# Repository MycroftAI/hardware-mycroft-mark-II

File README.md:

# Mycroft Mark II Hardware

*⛵️ Note that this repository is a work-in-progress. It will be updated and improved on over time.*

This repository contains all of the designs and technical details of the Mycroft Mark II Prototypes.

Each sub-directory represents a prototype device. Currently this consists of:
- [Mark II RPi OTS](./mark-II-rpi-ots) - the first Mark II prototype released in February 2020 made from off-the-shelf components. [Deprecated]
- [Mark II RPi DevKit](./mark-II-Rpi-devkit) - the second iteration of the Mark II prototype. This includes a custom daughterboard (SJ201) that integrates the components from the OTS prototype into a single PCB.

## Our open hardware principles
* **Copy our designs** – build your own Mycroft Mark 2 - Raspberry Pi Edition or its individual parts
* **Modify our designs** – remixing is encouraged
* **Sell products based on our designs** – commercial use is permitted
* **Always keep the open license** – contribute your output back to the community
* **Credit the original author(s)** – like they do in science

## Feedback or ideas

We are always keen to hear from the community about ways to improve these designs. Whether you're a hacker, maker, engineer, or something else - join us in the:
- [Community Forums](https://community.mycroft.ai)
- [Community Chat](https://chat.mycroft.ai)
- or email us at [dev@mycroft.ai](mailto:dev@mycroft.ai)

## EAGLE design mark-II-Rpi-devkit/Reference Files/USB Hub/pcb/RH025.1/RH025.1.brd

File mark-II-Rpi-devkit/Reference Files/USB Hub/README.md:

### Description

USB hub for the Raspberry Pi Zero

### Features

- 4 x USB 2.0 ports
- Micro USB upstream connector
- FE1.1s USB hub chip
- Solder pins for direct connection to the Raspberry Pi Zero
- Power jack connector for external 5v power source
- Optional jumpers to take power from upstream connector
- LED status indicators for each downstream port

### Modes of use

#### 1. Direct solder

You can solder 4 wires directly between the Zero and the hub using 4 pads exposed on both the hub and the Zero. This will connect the 5V, GND, USB D+ and USB D-.

You can then either power the board either using the USB power connector on the Zero, or using the power jack on the hub.

This is the neatest option, although does involve soldering.

#### 2. USB connection

Using a USB OTG cable, or a micro USB to micro USB you can connect the data USB port on the Zero to the upstream USB connector on the side of the hub. Adding the 2 power jumpers allows the hub to use power supplied to the Zero though the power USB connector.

Alternatively, remove the power jumpers and power the hub through the external power jack.

Although a USB cable is needed to connect the two in this mode, no soldering is required.

#### 3. Standalone hub

This board can be used as a regular USB hub, either using power from the upstream USB connector, or through the power jack and external power supply.

### Licence

This work is licensed under the Creative Commons Attribution-ShareAlike 4.0 International License. 
To view a copy of this license, visit http://creativecommons.org/licenses/by-sa/4.0/

Designed by <a xmlns:cc="http://creativecommons.org/ns#" href="http://www.richardhawthorn.com" property="cc:attributionName" rel="cc:attributionURL" target="_blank">Richard Hawthorn</a><br />

Based on design by @MakerBro, https://acrobotic.com

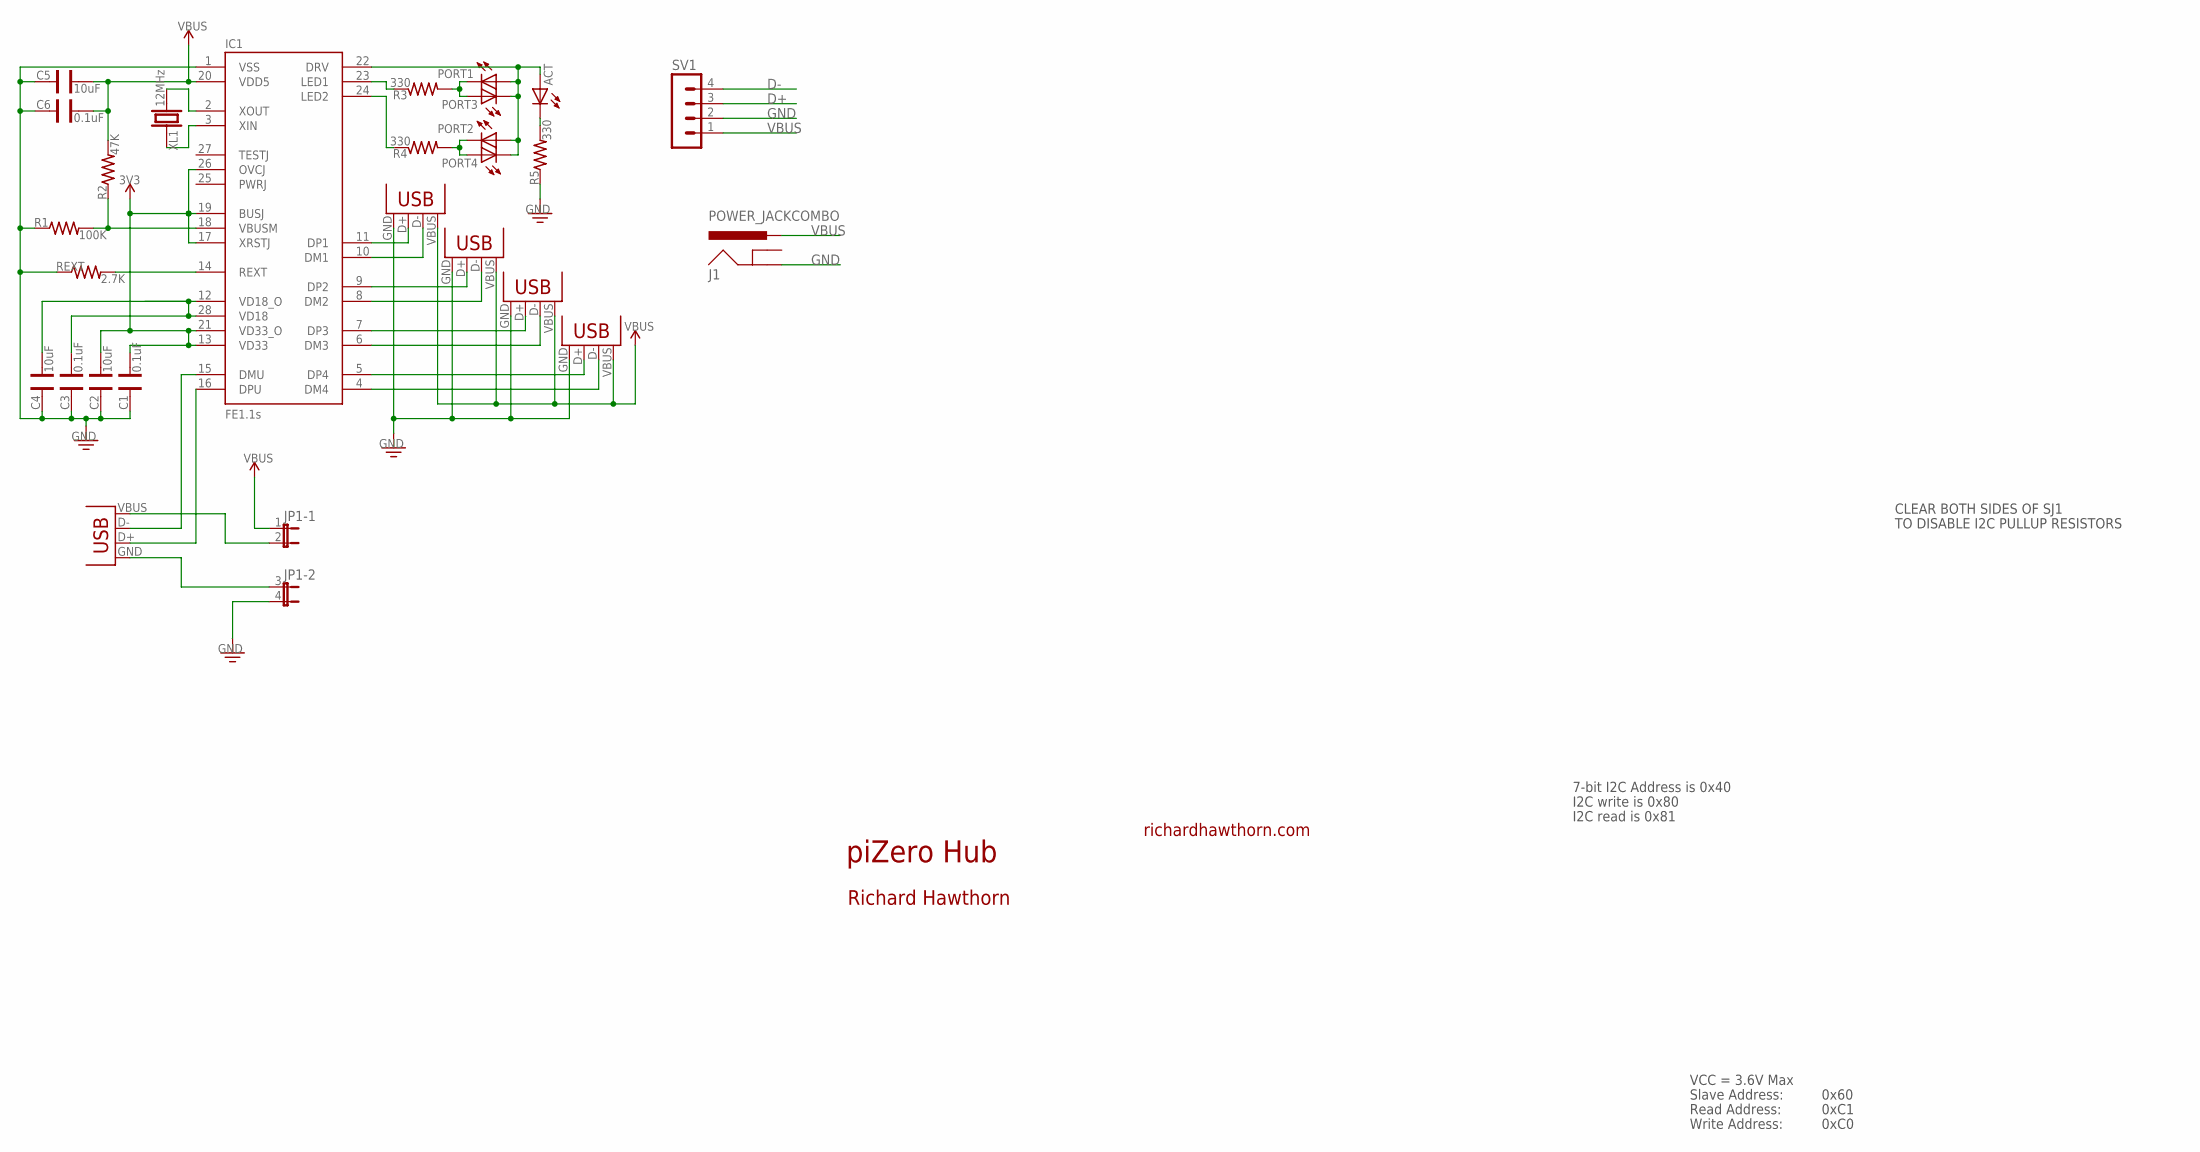
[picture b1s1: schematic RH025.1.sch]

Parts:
ACT: LED0603; LED-0603
C1, C3, C6: 0.1uF; CAP-0603
C2, C4, C5: 10uF; CAP-0603
IC1: FE1.1S; FE1.1S_SSOP-28
J1: POWER_JACKCOMBO; POWER_JACK_COMBO
JP1: JP2QE; JP2Q
PORT1, PORT2, PORT3, PORT4: LED0603; LED-0603
R1: 100K; RES-0603
R2: 47K; RES-0603
R3, R4, R5: 330; RES-0603
REXT: 2.7K; RES-0603
SV1: MA04-1
USB1: USBMICROB-PTH; USB-MICROB-TH
USB2, USB3, USB4, USB5: USBA-PTH; USB-A-F-PTH
XL1: 12MHz; HC49UP

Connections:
3V3: C1.1, C2.1, IC1.13 (VD33), IC1.17 (XRSTJ), IC1.19 (BUSJ), IC1.21 (VD33_O), IC1.26 (OVCJ)
D+: IC1.16 (DPU), SV1.3, USB1.D+
D-: IC1.15 (DMU), SV1.4, USB1.D-
GND: C1.2, C2.2, C3.2, C4.2, C5.2, C6.2, IC1.1 (VSS), J1.GND@1 (GND), JP1.4 (2), R1.1, R5.1, REXT.1, SV1.2, USB2.GND, USB3.GND, USB4.GND, USB5.GND
unnamed: IC1.14 (REXT), REXT.2
unnamed: JP1.2, USB1.VBUS
unnamed: JP1.3 (1), USB1.GND
unnamed: PORT2.C, PORT4.A, R4.2
unnamed: IC1.2 (XOUT), XL1.2
unnamed: C3.1, C4.1, IC1.12 (VD18_O), IC1.28 (VD18)
unnamed: IC1.3 (XIN), XL1.1
unnamed: IC1.11 (DP1), USB5.D+
unnamed: IC1.10 (DM1), USB5.D-
unnamed: IC1.18 (VBUSM), R1.2, R2.1
unnamed: IC1.9 (DP2), USB4.D+
unnamed: IC1.8 (DM2), USB4.D-
unnamed: IC1.7 (DP3), USB3.D+
unnamed: IC1.6 (DM3), USB3.D-
unnamed: IC1.5 (DP4), USB2.D+
unnamed: IC1.4 (DM4), USB2.D-
unnamed: PORT1.C, PORT3.A, R3.2
unnamed: ACT.C, R5.2
unnamed: IC1.23 (LED1), R3.1
unnamed: IC1.24 (LED2), R4.1
unnamed: ACT.A, IC1.22 (DRV), PORT1.A, PORT2.A, PORT3.C, PORT4.C
VBUS: C5.1, C6.1, IC1.20 (VDD5), J1.POWER (PWR), JP1.1, R2.2, SV1.1, USB2.VBUS, USB3.VBUS, USB4.VBUS, USB5.VBUS

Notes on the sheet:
piZero Hub
richardhawthorn.com
Richard Hawthorn
CLEAR BOTH SIDES OF SJ1
TO DISABLE I2C PULLUP RESISTORS
7-bit I2C Address is 0x40
I2C write is 0x80
I2C read is 0x81
VCC = 3.6V Max
Read Address:
Write Address:
Slave Address:
0x60
0xC1
0xC0

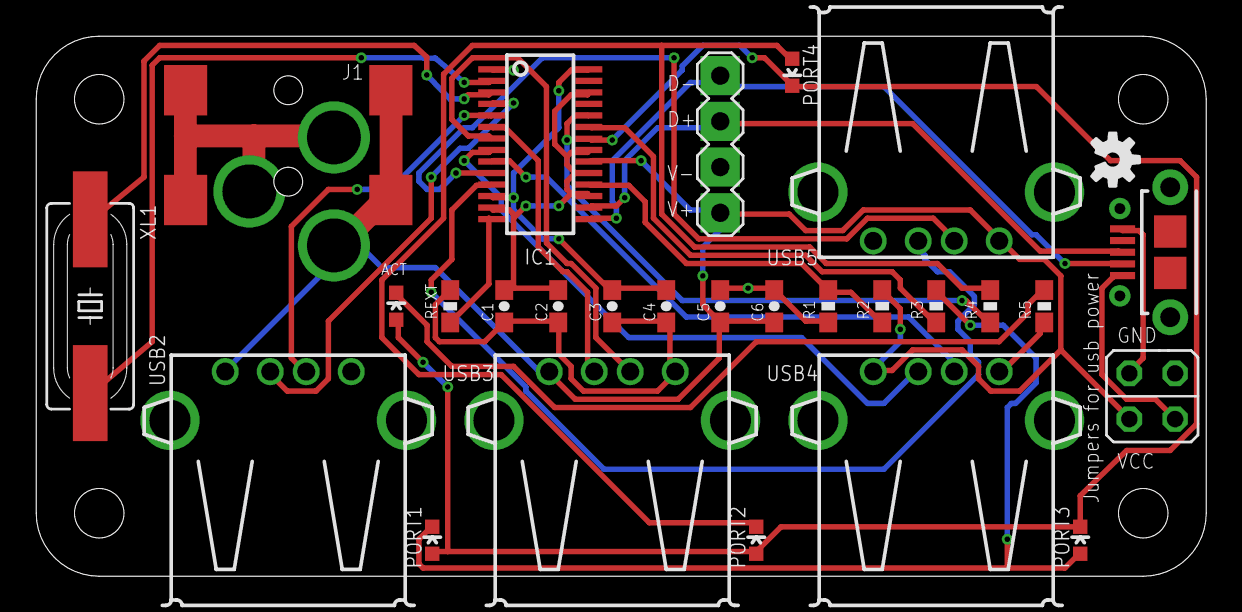
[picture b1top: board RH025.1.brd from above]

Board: 2 copper layers, 65.0 x 30.0 mm, 28 parts (0 on the bottom side), 26 nets.

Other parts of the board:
U$3: OSHW-LOGO-S

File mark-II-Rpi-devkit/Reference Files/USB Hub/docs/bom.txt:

Partlist

Qty Value           Device          Package          Parts                                             
5   LED             LED0603         LED-0603         ACT, PORT1, PORT2, PORT3, PORT4                             
3   0.1uF           CAP0603         CAP-0603         C1, C3, C6                                          
1   100K            RES0603         RES-0603         R1                              
3   10uF            CAP0603         CAP-0603         C2, C4, C5                                          
1   12MHz           CRYSTALHC49UP   HC49UP           XL1                                    
1   2.7K            RES0603         RES-0603         REXT                            
3   330r            RES0603         RES-0603         R3, R4, R5                      
1   47K             RES0603         RES-0603         R2                              
1   FE1.1S          FE1.1S          FE1.1S_SSOP-28   IC1                                                 
1   POWER_JACKCOMBO POWER_JACKCOMBO POWER_JACK_COMBO J1                                  
4   USBA-PTH        USBA-PTH        USB-A-F-PTH      USB2, USB3, USB4, USB5                              
1   USBMICROB-PTH   USBMICROB-PTH   USB-MICROB-TH    USB1

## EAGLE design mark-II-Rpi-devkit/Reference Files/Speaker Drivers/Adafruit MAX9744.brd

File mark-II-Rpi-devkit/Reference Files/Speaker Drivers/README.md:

# PCB files for Adafruit MAX9744 20W stereo audio amplifier board

<a href="http://www.adafruit.com/products/1752"><br/>Click here to purchase one from the Adafruit shop</a>

Pump up the volume with this 20W stereo amplifier! This slim little board has a class D amplifier onboard that can drive 2 channels of 4-8 ohm impedance speakers at 20W each. Power it with 5-12VDC using the onboard DC power jack and plug stereo line level into the 3.5mm stereo headphone jack and jam out with ease. Since it's class D, its completely cool-running, no heat sinks are required and it's extremely efficient - up to 93% efficiency makes it great for portable or battery powered rigs.

We like the MAX9744 amplifier at the heart of this board because its very easy to use, but it also has both analog and digital volume control capability. Use a single 1K½ pot (we include one) to adjust volume analog-style. Or hook it up to your favorite microcontroller and send I2C commands to set 64-steps of volume amplification.

Some great stats about the MAX9744:

- Power from 4.5V-14V DC voltage
- Up to 93% efficient (88-93% typical)
- 20mA quiescent current (or put into shutdown for 1uA quiescent)
- Up to 29.5dB max gain
- Use DC or AC coupled line-level input, up to 3Vpp
- Filterless Spread-Spectrum Modulation Lowers
- Radiated RF Emissions from Speaker Cables
- 20W Stereo Output (4, VDD = 12V, THD+N = 10%)
- Low 0.04% THD+N
- Integrated Click-and-Pop Suppression
- Short-Circuit and Thermal-Overload Protection

We took this lovely chip and wrapped it up into a breakout for you, with polarity-protection, jacks and terminal blocks, i2c level shifting, and a spot to solder in a volume pot.

Each order comes with one MAX9744 breakout board with all surface-mount parts fully assembled and tested. We also include 3 x 2pin and 1 x 3pin terminal blocks, a 470uF power filter capacitor and 1K½ trim pot. To use this board, a little soldering is required to attach the terminal blocks and other components, but its fairly easy and expect it should take less than 15 minutes. [Check out our detailed tutorial for assembly instructions and overall usage](http://learn.adafruit.com/adafruit-20w-stereo-audio-amplifier-class-d-max9744).

Note: The terminal blocks included with your product may be blue or black.

## License

Adafruit invests time and resources providing this open source design, 
please support Adafruit and open-source hardware by purchasing 
products from Adafruit!

Designed by Adafruit Industries.  
Creative Commons Attribution, Share-Alike license, check license.txt for more information
All text above must be included in any redistribution

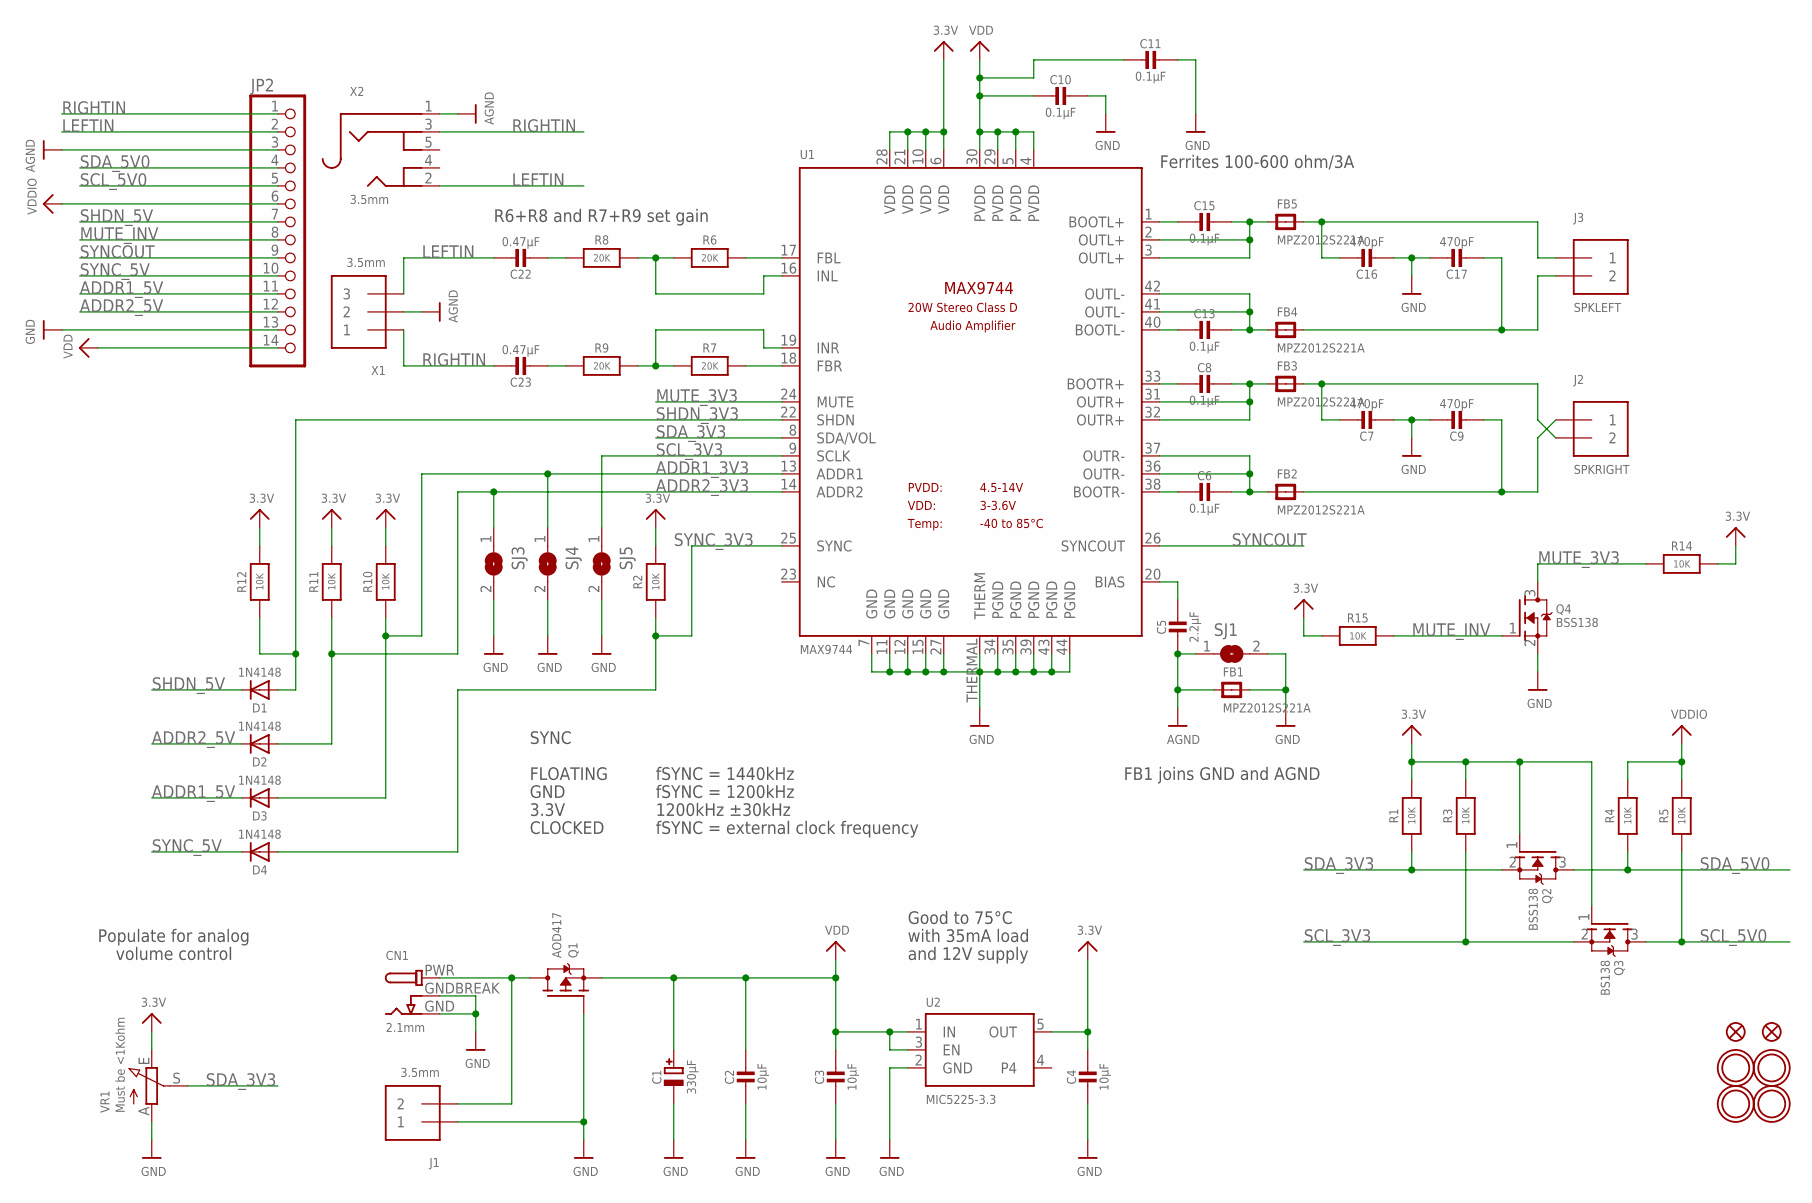
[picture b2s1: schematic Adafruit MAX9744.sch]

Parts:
C1: 330µF; CELEC_3.5MM_8MM
C2, C3, C4: 10µF; 0805-NO
C5: 2.2µF; 0805-NO
C6, C8, C10, C11, C13, C15: 0.1µF; 0805-NO
C7, C9, C16, C17: 470pF; 0805-NO
C22, C23: 0.47µF; 0805-NO
CN1: 2.1mm; DCJACK_2MM_SMT
D1, D2, D3, D4: 1N4148; SOD-323
FB1, FB2, FB3, FB4, FB5: MPZ2012S221A; _0805
FID1, FID2: FIDUCIAL""; FIDUCIAL_1MM
J1: 3.5mm; TERMBLOCK_1X2-3.5MM
J2: SPKRIGHT; TERMBLOCK_1X2-3.5MM
J3: SPKLEFT; TERMBLOCK_1X2-3.5MM
JP2: HEADER-1X14; 1X14_ROUND70
Q1: AOD417; TO252
Q2, Q4: BSS138; SOT23-WIDE
Q3: BS138; SOT23-WIDE
R1, R3, R4, R5, R12: 10K; 0805-NO
R2, R10, R11, R14, R15: 10K; _0805MP
R6, R7, R8, R9: 20K; 0805-NO
SJ1, SJ3, SJ4, SJ5: SOLDERJUMPER; SOLDERJUMPER_ARROW_NOPASTE
U1: MAX9744; TQFN44_7MM
U2: MIC5225-3.3; SOT23-5
U$29, U$38, U$39, U$40: MOUNTINGHOLE2.5_THICK; MOUNTINGHOLE_2.5_PLATED_THICK
VR1: Must be <1Kohm; TRIMPOT_100MILPTH
X1: 3.5mm; TERMBLOCK_1X3-3.5MM
X2: 3.5mm; 4UCONN_19269

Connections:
3.3V: C4.1, Q2.1 (G), Q3.1 (G), R1.2, R2.2, R3.2, R10.2, R11.2, R12.2, R14.2, R15.1, U1.6 (VDD), U1.10 (VDD), U1.21 (VDD), U1.28 (VDD), U2.5 (OUT), VR1.E
ADDR1_3V3: D3.A, R10.1, SJ4.1, U1.13 (ADDR1)
ADDR1_5V: D3.C, JP2.11
ADDR2_3V3: D2.A, R11.1, SJ3.1, U1.14 (ADDR2)
ADDR2_5V: D2.C, JP2.12
AGND: C5.2, FB1.1, JP2.3, SJ1.1, X1.2, X2.1
GND: C1.-, C2.2, C3.2, C4.2, C7.2, C9.1, C10.1, C11.1, C16.2, C17.1, CN1.GND, CN1.GNDBREAK, FB1.2, J1.1, JP2.13, Q1.1 (G), Q4.2 (S), SJ1.2, SJ3.2, SJ4.2, SJ5.2, U1.7 (GND), U1.11 (GND), U1.12 (GND), U1.15 (GND), U1.27 (GND), U1.34 (PGND), U1.35 (PGND), U1.39 (PGND), U1.43 (PGND), U1.44 (PGND), U1.THERMAL (THERM), U2.2 (GND), VR1.A
LEFTIN: C22.1, JP2.2, X1.3, X2.2
MUTE_3V3: Q4.3 (D), R14.1, U1.24 (MUTE)
MUTE_INV: JP2.8, Q4.1 (G), R15.2
unnamed: CN1.PWR, J1.2, Q1.3 (D)
unnamed: C5.1, U1.20 (BIAS)
unnamed: C6.2, U1.38 (BOOTR-)
unnamed: C6.1, FB2.1, U1.36 (OUTR-), U1.37 (OUTR-)
unnamed: C8.2, U1.33 (BOOTR+)
unnamed: C8.1, FB3.1, U1.31 (OUTR+), U1.32 (OUTR+)
unnamed: C7.1, FB3.2, J2.2
unnamed: C9.2, FB2.2, J2.1
unnamed: C13.1, FB4.1, U1.41 (OUTL-), U1.42 (OUTL-)
unnamed: C15.1, FB5.1, U1.2 (OUTL+), U1.3 (OUTL+)
unnamed: C16.1, FB5.2, J3.1
unnamed: C17.2, FB4.2, J3.2
unnamed: C15.2, U1.1 (BOOTL+)
unnamed: C13.2, U1.40 (BOOTL-)
unnamed: R6.2, U1.17 (FBL)
unnamed: R7.2, U1.18 (FBR)
unnamed: R6.1, R8.2, U1.16 (INL)
unnamed: R7.1, R9.2, U1.19 (INR)
unnamed: C22.2, R8.1
unnamed: C23.2, R9.1
RIGHTIN: C23.1, JP2.1, X1.1, X2.3
SCL_3V3: Q3.2 (S), R3.1, SJ5.1, U1.9 (SCLK)
SCL_5V0: JP2.5, Q3.3 (D), R5.1
SDA_3V3: Q2.2 (S), R1.1, U1.8 (SDA/VOL), VR1.S
SDA_5V0: JP2.4, Q2.3 (D), R4.1
SHDN_3V3: D1.A, R12.1, U1.22 (SHDN)
SHDN_5V: D1.C, JP2.7
SYNCOUT: JP2.9, U1.26 (SYNCOUT)
SYNC_3V3: D4.A, R2.1, U1.25 (SYNC)
SYNC_5V: D4.C, JP2.10
VDD: C1.+, C2.1, C3.1, C10.2, C11.2, JP2.14, Q1.2 (S), U1.4 (PVDD), U1.5 (PVDD), U1.29 (PVDD), U1.30 (PVDD), U2.1 (IN), U2.3 (EN)
VDDIO: JP2.6, R4.2, R5.2

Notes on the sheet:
Good to 75°C
with 35mA load
and 12V supply
FB1 joins GND and AGND
SYNC
FLOATING
GND
3.3V
CLOCKED
fSYNC = 1200kHz
fSYNC = 1440kHz
1200kHz ±30kHz
fSYNC = external clock frequency
R6+R8 and R7+R9 set gain
Ferrites 100-600 ohm/3A
Populate for analog
volume control

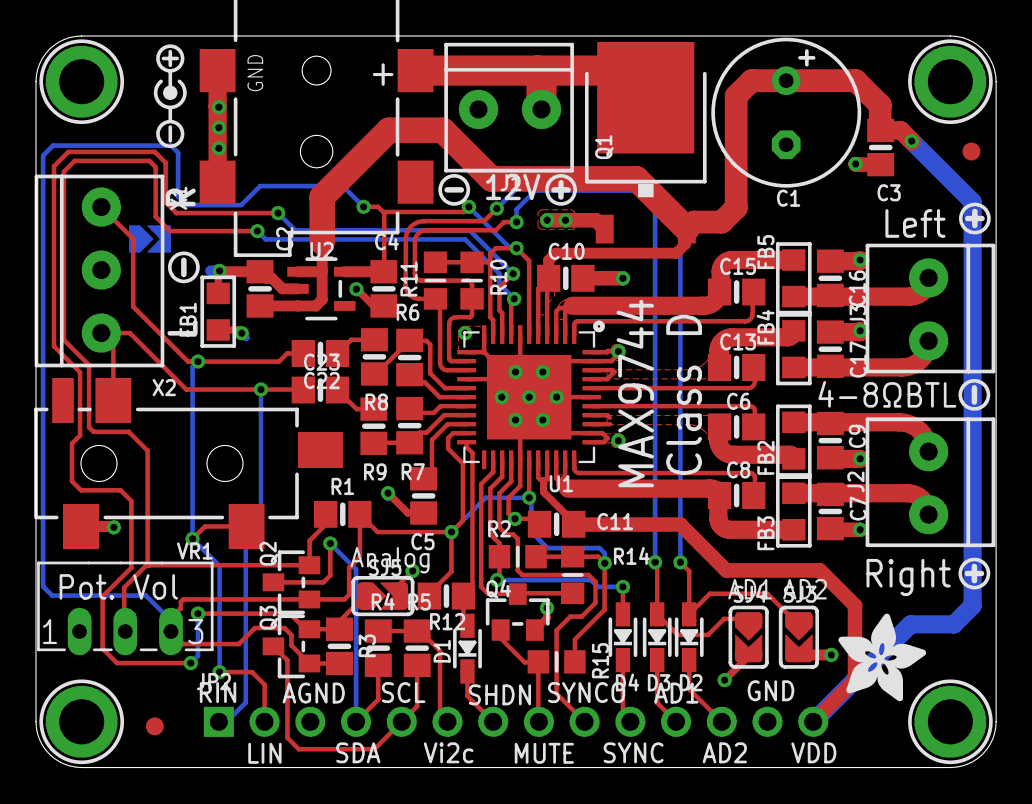
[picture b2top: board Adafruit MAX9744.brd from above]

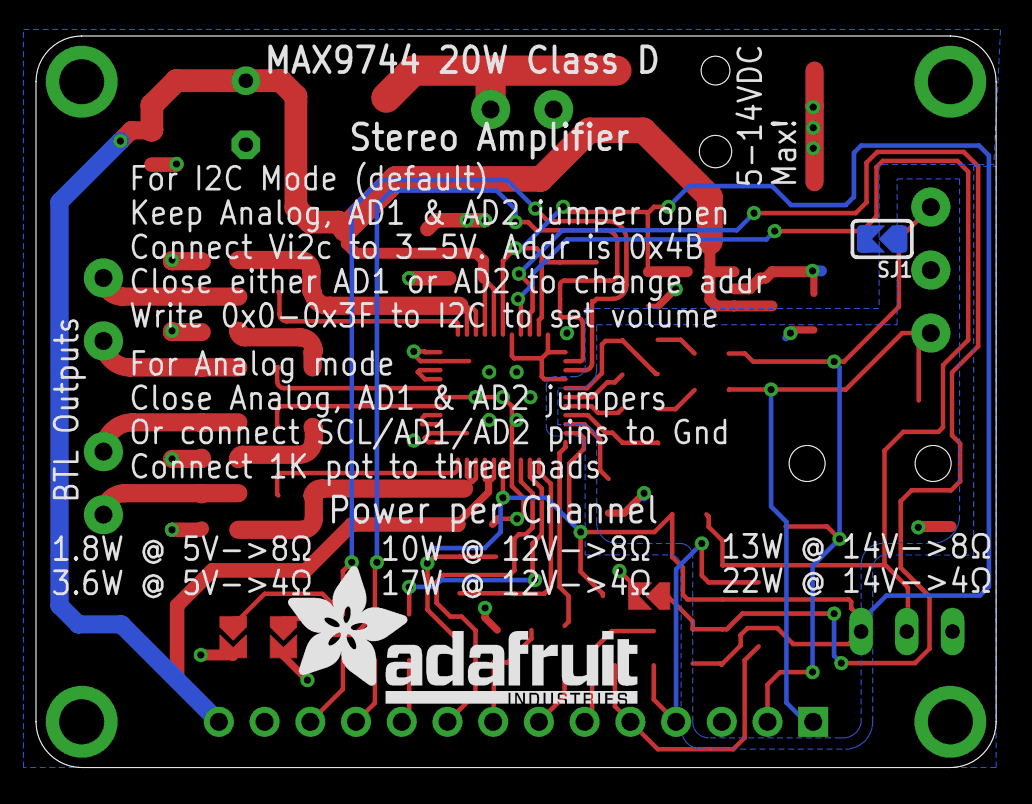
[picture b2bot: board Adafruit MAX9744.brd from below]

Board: 2 copper layers, 53.3 x 40.6 mm, 73 parts (2 on the bottom side), 42 nets.

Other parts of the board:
U$28: ADAFRUIT_TEXT_20MM
U$32: ADAFRUIT_5MM
U$41: ICON_POSITIVE_CENTER-M
U$42, U$50, U$52: ICON_PLUS
U$43, U$47, U$51: ICON_MINUS

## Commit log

2020-01-28 Create BOM
2020-01-28 Update BOM
2020-01-30 Rename instructions.md to Instructions.md
2020-01-30 Create STL
2020-01-30 Create STP
2020-01-30 Rename STP to STP.md
2020-01-30 Rename STL to STL.md
2020-07-14 Create mark-II-Rpi-OTS
2020-07-14 reorganizing files
    Renamed repo to hard-ware-mycroft-mark-II to encompass all Mark II hardware projects, and renamed Mark-II-rpi-prototype to Mark-II-rpi-ots. Created mark-II-rpi-devkit for the current raspberry pi bas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
2020-07-14 Initial Design
2020-07-15 Replace SMD 40pin header, replace with Thru Hole version
2020-07-15 update version number
    update version number
2020-07-15 add repo overview
2020-07-15 cleanup and shift info to component dir
2020-07-15 fix image paths
2020-07-15 add call for feedback
2020-07-15 fix broken link
2020-07-15 Update BOM - fix OPL numbers for Seeed PCBA
2020-07-15 fix library so only using 0.3mm drill and bigger
2020-07-22 Updated KiCAD files to 0.63 for PCB printing & Assembly at JLCPCB
2020-07-22 Add updated PCB Renders
2020-07-24 Change USB IC to CM108B, add in Line Out jack, prep for 2 PCB sandwich
2020-07-24 Change vertical barrel connector, files sent to JLC PCB for printing and assembly.
2020-07-24 Update Readme with renders
2020-08-08 Mark 2 - PCB Files to the printer
2020-08-17 Update to v0.66 - printed at JLC - 2nd spin
2020-08-29 Fix missing library path
2020-08-29 Fix missing items in schematic in Github
2020-08-29 Fix missing items in schematic in Github - add in libraries
2020-09-04 Add in USB Adapter - SJ-202
2020-09-09 Update part numbers and links
2020-09-16 Add in testing scripts for SJ-201
2020-09-27 SJ201 - Removed CM108b soundcard, added in I2S to Line out, ATTin402. Moved holes in layout. SJ202 - extened length to plug into USB2.0 port
2020-09-27 SJ201 Move BOM files into BOM folder
2020-10-08 SJ-201 v3, sent to PCB Fab. Removed USB Hub, add in I2S to Line Out
2020-10-08 SJ-202 USB Jumper Update & Readme updates
2020-10-08 Readme updates
2020-11-20 Rev4 Update - Add in Coral TPU, TAS5806, remove I2S * MAX9744. Change Attiny to Attin1614
2020-11-23 Rev4 Update - fix some wiring, export for printing Rev 4
2020-12-11 Update README.md
    fix images
2020-12-11 Update README.md
    Updated for Rev 4 board specs.
2020-12-12 Update README.md
    Updated (partially) for R4
2020-12-30 add standard license and move to subdirectory
2021-01-02 SJ-201-R6 for FAB - removed buffer IC
2021-02-19 Update eeprom_update.sh
    2021-02-19 - J.M. - Improved Docs
2021-03-04 Updated files for R6 v2
2021-03-04 deprecated OTS HW
2021-03-04 deprecated this design
2021-03-04 removed USB mode
    The USB on the Pi 4 was unreliable for real-time audio data.
2021-03-04 Updated to match version 6.02.
    Also removed part numbering and "related parts" sections.
2021-03-04 not used in Rev 6 design
2021-03-04 removed WIP note
2021-03-04 Added in test jig scripts, update ATTiny Code
2021-03-04 Remove extra images folder, add in Gerbers
2021-03-04 Update Reference Files, remove unused parts
2021-03-05 Update part datasheet for 12v power to 5v
2021-03-05 Rename readme to readme.md
2021-03-08 Cleaned up SJ201 directory
2021-03-08 Removed unused files, cleaned up directory, remove SJ202
2021-03-08 Add back Readme
2021-03-08 Bugfix
2021-03-08 Removed redundant files
2021-03-09 fix dependency issue
2021-03-14 Update libraries, reorganize files
2021-03-18 Create MkII SJ240 SW19 r9.zip
    Added Zip containing STEP files of the SJ240 R9 enclosure
2021-03-19 Bump pillow from 7.1.2 to 8.1.1 in /mark-II-Rpi-devkit/code/TestingJig
    Bumps [pillow](https://github.com/python-pillow/Pillow) from 7.1.2 to 8.1.1.
    - [Release notes](https://github.com/python-pillow/Pillow/releases)
    - [Changelog](https://github.com/python-pillow/Pillow/blob/master/CHANGES.rst)
    - [Commits](https://github.com/python-pillow/Pillow/compare/7.1.2...8.1.1)
2021-06-02 Bump urllib3 in /mark-II-Rpi-devkit/code/TestingJig
    Bumps [urllib3](https://github.com/urllib3/urllib3) from 1.24.3 to 1.26.5.
    - [Release notes](https://github.com/urllib3/urllib3/releases)
    - [Changelog](https://github.com/urllib3/urllib3/blob/main/CHANGES.rst)
    - [Commits](https://github.com/urllib3/urllib3/compare/1.24.3...1.26.5)
    ---
    updated-dependencies:
2021-06-08 Bump pillow from 7.1.2 to 8.2.0 in /mark-II-Rpi-devkit/code/TestingJig
    Bumps [pillow](https://github.com/python-pillow/Pillow) from 7.1.2 to 8.2.0.
    - [Release notes](https://github.com/python-pillow/Pillow/releases)
    - [Changelog](https://github.com/python-pillow/Pillow/blob/master/CHANGES.rst)
    - [Commits](https://github.com/python-pillow/Pillow/compare/7.1.2...8.2.0)
    ---
    updated-dependencies:
2021-09-08 Bump pillow from 7.1.2 to 8.3.2 in /mark-II-Rpi-devkit/code/TestingJig
    Bumps [pillow](https://github.com/python-pillow/Pillow) from 7.1.2 to 8.3.2.
    - [Release notes](https://github.com/python-pillow/Pillow/releases)
    - [Changelog](https://github.com/python-pillow/Pillow/blob/master/CHANGES.rst)
    - [Commits](https://github.com/python-pillow/Pillow/compare/7.1.2...8.3.2)
    ---
    updated-dependencies:
2021-10-21 Bump babel from 2.9.0 to 2.9.1 in /mark-II-Rpi-devkit/code/TestingJig
    Bumps [babel](https://github.com/python-babel/babel) from 2.9.0 to 2.9.1.
    - [Release notes](https://github.com/python-babel/babel/releases)
    - [Changelog](https://github.com/python-babel/babel/blob/master/CHANGES)
    - [Commits](https://github.com/python-babel/babel/compare/v2.9.0...v2.9.1)
    ---
    updated-dependencies:
2021-11-08 MII AC spacer
    Added AC Spacer for SJ240 3D printed design
2021-11-11 Update checklist for SJ-201-R7
2021-12-07 Added Speaker Spacer for alternate speaker driver
2021-12-07 Audio Chamber for SJ230 (laser cut enclosure)
2022-01-13 Bump pillow from 7.1.2 to 9.0.0 in /mark-II-Rpi-devkit/code/TestingJig
    Bumps [pillow](https://github.com/python-pillow/Pillow) from 7.1.2 to 9.0.0.
    - [Release notes](https://github.com/python-pillow/Pillow/releases)
    - [Changelog](https://github.com/python-pillow/Pillow/blob/main/CHANGES.rst)
    - [Commits](https://github.com/python-pillow/Pillow/compare/7.1.2...9.0.0)
    ---
    updated-dependencies:
2022-02-25 Revision 8 changes
    remove I2S headphone output jack
2022-03-12 Bump pillow from 7.1.2 to 9.0.1 in /mark-II-Rpi-devkit/code/TestingJig
    Bumps [pillow](https://github.com/python-pillow/Pillow) from 7.1.2 to 9.0.1.
    - [Release notes](https://github.com/python-pillow/Pillow/releases)
    - [Changelog](https://github.com/python-pillow/Pillow/blob/main/CHANGES.rst)
    - [Commits](https://github.com/python-pillow/Pillow/compare/7.1.2...9.0.1)
    ---
    updated-dependencies:
2022-05-25 Bump pyjwt from 1.7.1 to 2.4.0 in /mark-II-Rpi-devkit/code/TestingJig
    Bumps [pyjwt](https://github.com/jpadilla/pyjwt) from 1.7.1 to 2.4.0.
    - [Release notes](https://github.com/jpadilla/pyjwt/releases)
    - [Changelog](https://github.com/jpadilla/pyjwt/blob/master/CHANGELOG.rst)
    - [Commits](https://github.com/jpadilla/pyjwt/compare/1.7.1...2.4.0)
    ---
    updated-dependencies:
2022-06-22 Bump numpy from 1.20.1 to 1.22.0 in /mark-II-Rpi-devkit/code/TestingJig
    Bumps [numpy](https://github.com/numpy/numpy) from 1.20.1 to 1.22.0.
    - [Release notes](https://github.com/numpy/numpy/releases)
    - [Changelog](https://github.com/numpy/numpy/blob/main/doc/HOWTO_RELEASE.rst)
    - [Commits](https://github.com/numpy/numpy/compare/v1.20.1...v1.22.0)
    ---
    updated-dependencies:
2022-06-28 Bump arrow from 0.12.0 to 0.15.1 in /mark-II-Rpi-devkit/code/TestingJig
    Bumps [arrow](https://github.com/arrow-py/arrow) from 0.12.0 to 0.15.1.
    - [Release notes](https://github.com/arrow-py/arrow/releases)
    - [Changelog](https://github.com/arrow-py/arrow/blob/master/CHANGELOG.rst)
    - [Commits](https://github.com/arrow-py/arrow/compare/0.12.0...0.15.1)
    ---
    updated-dependencies:
2022-09-23 Add SJ240 3D print files
    The SJ240 is the 3D printed enclosure.
    These STL files can be used to print an enclosure for the Mark II Dev Kit.
    Note that screws and threaded inserts are also required.
2022-09-23 Add info on 3D print files
    Includes link to appropriate threaded inserts
2022-09-23 Add link to Instructables for 3D printed case
2022-09-23 Bump protobuf in /mark-II-Rpi-devkit/code/TestingJig
    Bumps [protobuf](https://github.com/protocolbuffers/protobuf) from 3.15.2 to 3.18.3.
    - [Release notes](https://github.com/protocolbuffers/protobuf/releases)
    - [Changelog](https://github.com/protocolbuffers/protobuf/blob/main/generate_changelog.py)
    - [Commits](https://github.com/protocolbuffers/protobuf/compare/v3.15.2...v3.18.3)
    ---
    updated-dependencies:
2022-10-22 SJ-201-R10
2022-10-25 BOM for SJ-201-R10
2022-11-22 Bump pillow from 7.1.2 to 9.3.0 in /mark-II-Rpi-devkit/code/TestingJig
    Bumps [pillow](https://github.com/python-pillow/Pillow) from 7.1.2 to 9.3.0.
    - [Release notes](https://github.com/python-pillow/Pillow/releases)
    - [Changelog](https://github.com/python-pillow/Pillow/blob/main/CHANGES.rst)
    - [Commits](https://github.com/python-pillow/Pillow/compare/7.1.2...9.3.0)
    ---
    updated-dependencies:
2022-12-08 Bump certifi in /mark-II-Rpi-devkit/code/TestingJig
    Bumps [certifi](https://github.com/certifi/python-certifi) from 2020.12.5 to 2022.12.7.
    - [Release notes](https://github.com/certifi/python-certifi/releases)
    - [Commits](https://github.com/certifi/python-certifi/compare/2020.12.05...2022.12.07)
    ---
    updated-dependencies:
    - dependency-name: certifi
2023-02-08 Bump cryptography in /mark-II-Rpi-devkit/code/TestingJig
    Bumps [cryptography](https://github.com/pyca/cryptography) from 3.4.6 to 39.0.1.
    - [Release notes](https://github.com/pyca/cryptography/releases)
    - [Changelog](https://github.com/pyca/cryptography/blob/main/CHANGELOG.rst)
    - [Commits](https://github.com/pyca/cryptography/compare/3.4.6...39.0.1)
    ---
    updated-dependencies:
2023-02-20 Create MkII SJ250 ASSEM r6.zip
    Mark II production mechanical CAD full assembly in STEP format
2023-02-24 add body assembly instructions
2023-02-24 add images for body assembly
2023-02-24 remove unusable sizing parameters from images
2023-02-24 add breaks before and after images
2023-02-24 upload top, speaker and display assembly images
2023-02-24 formatting tweaks to top assembly instructions
2023-02-24 add speaker and display assembly instructions
2023-02-24 correct image links
2023-02-24 Rename mark-ii-assembly.md to README.md
2023-06-13 Added KiCAD layout file

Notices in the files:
parts and their libraries:
microbuilder: This work is placed in the public domain, and may be freely used for commercial and non-commercial work with the following conditions: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
SparkFun-Aesthetics: Licensing: CC v3.0 Share-Alike You are welcome to use this library for commercial purposes.
